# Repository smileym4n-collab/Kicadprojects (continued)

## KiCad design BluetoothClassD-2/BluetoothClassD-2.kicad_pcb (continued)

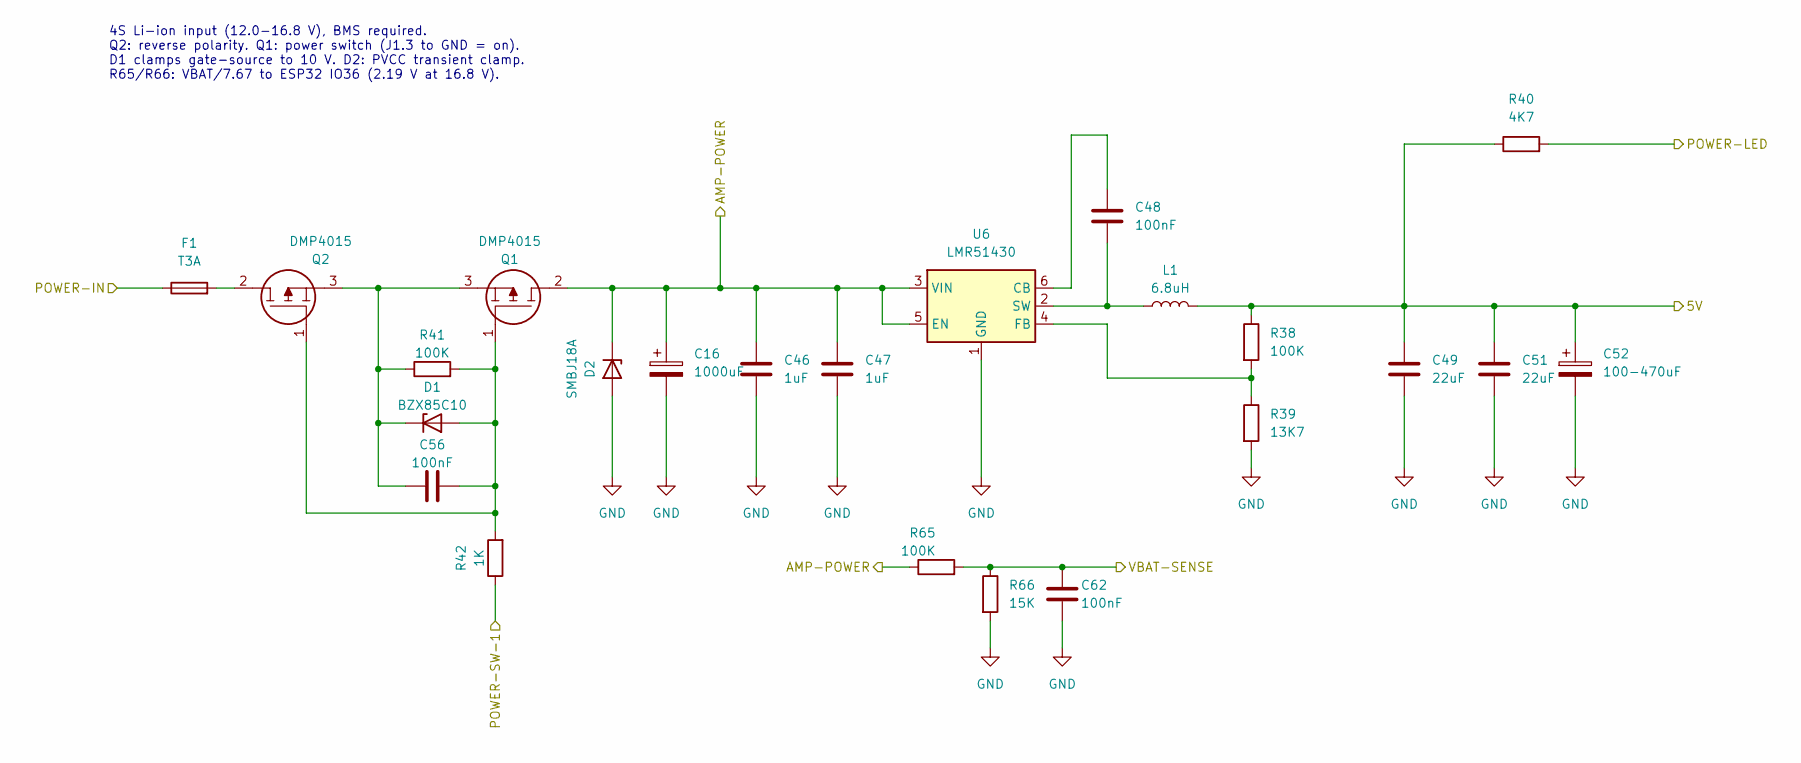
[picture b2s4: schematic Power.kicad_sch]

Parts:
C16: 1000uF; CP_Radial_D13.0mm_P5.00mm
C46, C47: 1uF; C_1206_3216Metric_Pad1.33x1.80mm_HandSolder
C48: 100nF; C_1206_3216Metric_Pad1.33x1.80mm_HandSolder
C49, C51: 22uF; C_1206_3216Metric_Pad1.33x1.80mm_HandSolder
C52: 100-470uF; CP_Radial_D8.0mm_P3.50mm
C56, C62: 100nF; C_0603_1608Metric_Pad1.08x0.95mm_HandSolder
D1: BZX85C10; D_DO-41_SOD81_P10.16mm_Horizontal; Manufacturer_Part_Number BZX85C10
D2: SMBJ18A; D_SMB; Manufacturer_Part_Number SMBJ18A
F1: T3A; Fuse_1206_3216Metric_Pad1.42x1.75mm_HandSolder
L1: 6.8uH; SRP6030WA-6R8M
Q1, Q2: DMP4015; DMP4015SK313; Manufacturer_Part_Number DMP4015SK3-13
R38, R41: 100K; R_0805_2012Metric_Pad1.20x1.40mm_HandSolder
R39: 13K7; R_0805_2012Metric_Pad1.20x1.40mm_HandSolder
R40: 4K7; R_0805_2012Metric_Pad1.20x1.40mm_HandSolder
R42: 1K; R_0805_2012Metric_Pad1.20x1.40mm_HandSolder
R65: 100K; R_0805_2012Metric_Pad1.20x1.40mm_HandSolder; Manufacturer_Part_Number RT0805DRE07100KL
R66: 15K; R_0805_2012Metric_Pad1.20x1.40mm_HandSolder; Manufacturer_Part_Number RR1220P-153-D
U6: LMR51430; SOT-23-6_Handsoldering

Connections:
/Amp/PVCC: C16.1, C46.1, C47.1, D2.1 (K), Q1.2, R65.1, U6.3 (VIN), U6.5 (EN); also elsewhere on the board
/DAC/5V: C49.1, C51.1, C52.1, L1.2, R38.1, R40.1; also elsewhere on the board
/ESP32/VBAT-SENSE: C62.1, R65.2, R66.1; also elsewhere on the board
/POWER-IN: F1.1; also elsewhere on the board
/POWER-LED: R40.2; also elsewhere on the board
/POWER-SW1: R42.1; also elsewhere on the board
GND: C16.2, C46.2, C47.2, C49.2, C51.2, C52.2, C62.2, D2.2 (A), R39.2, R66.2, U6.1 (GND); also elsewhere on the board
unnamed: C56.2, D1.2 (A), Q1.1, Q2.1, R41.2, R42.2
unnamed: C56.1, D1.1 (K), Q1.3, Q2.3, R41.1
unnamed: F1.2, Q2.2
unnamed: C48.1, U6.6 (CB)
unnamed: R38.2, R39.1, U6.4 (FB)
unnamed: C48.2, L1.1, U6.2 (SW)

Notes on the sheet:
4S Li-ion input (12.0-16.8 V), BMS required. Q2: reverse polarity. Q1: power switch (J1.3 to GND = on). D1 clamps gate-source to 10 V. D2: PVCC transient clamp. R65/R66: VBAT/7.67 to ESP32 IO36 (2.19 V at 16.8 V).

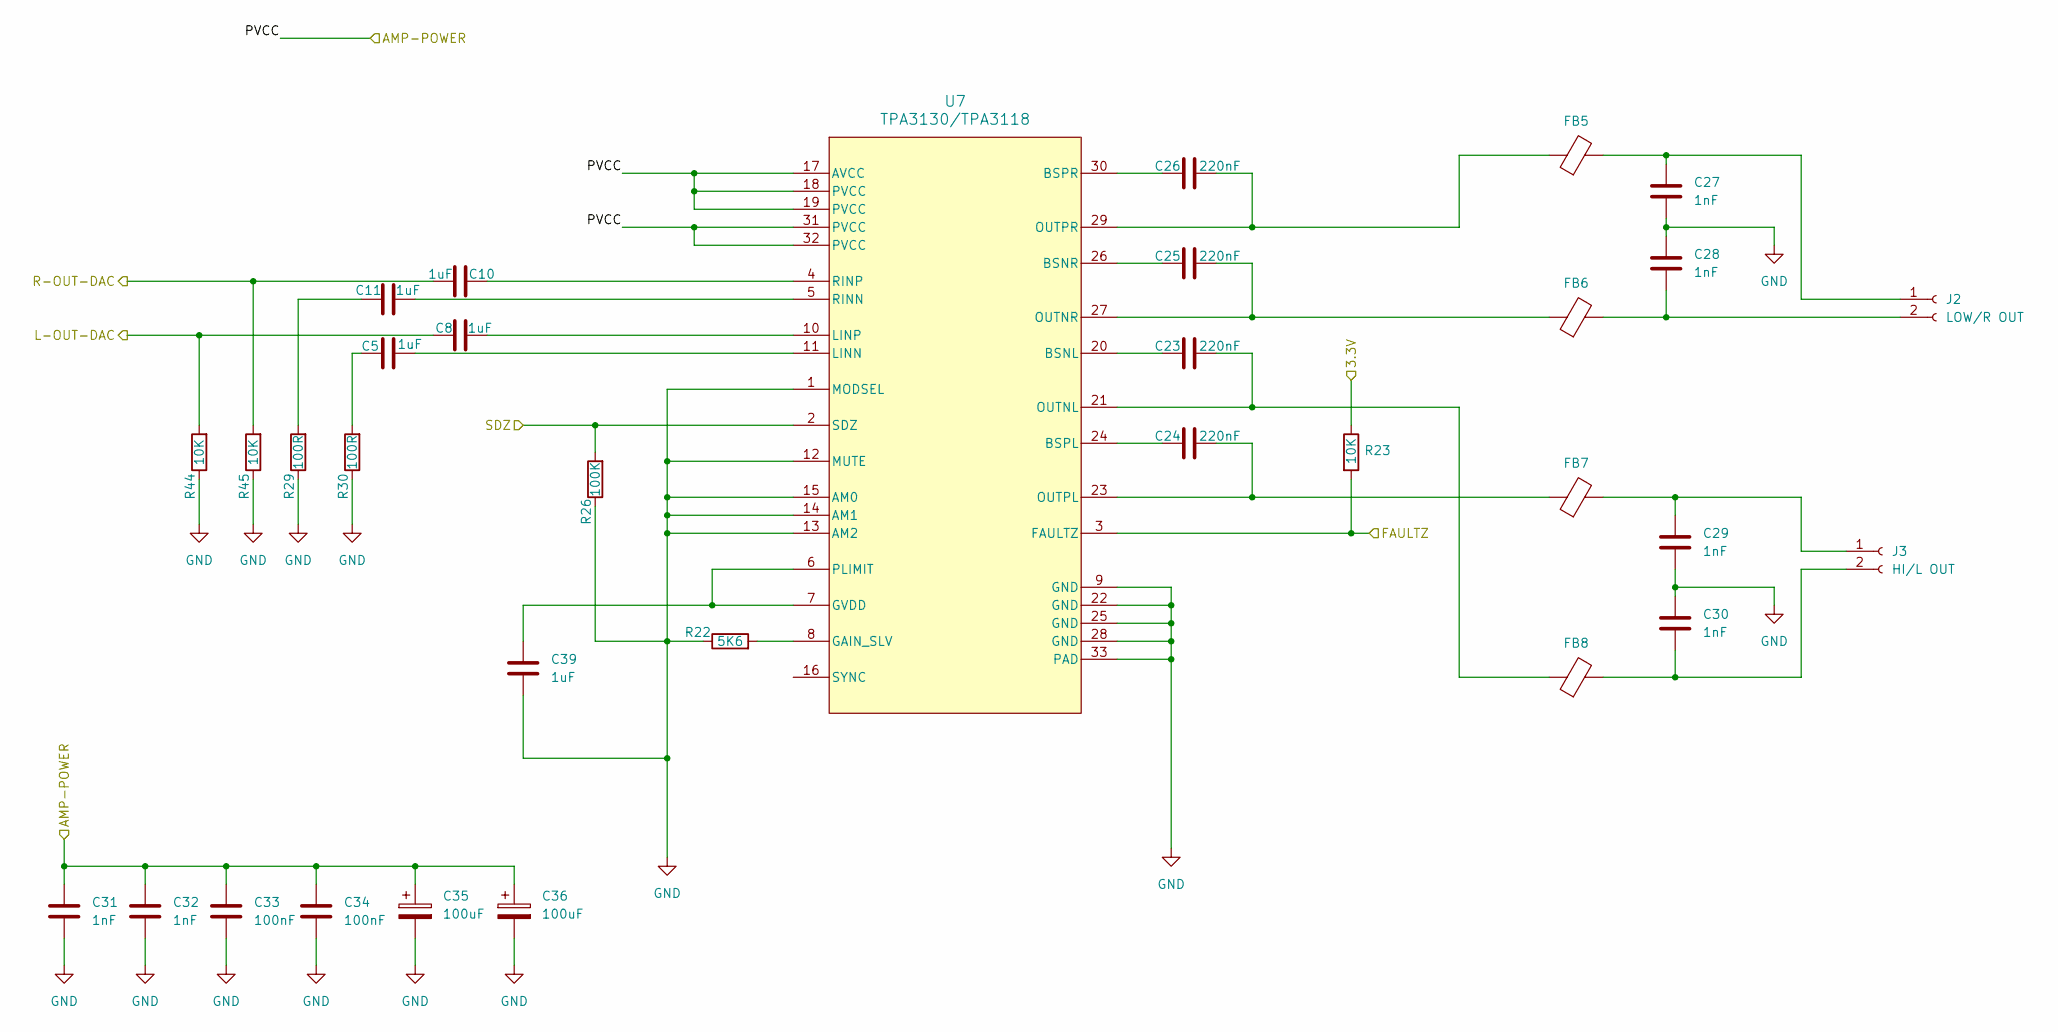
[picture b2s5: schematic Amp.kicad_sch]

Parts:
C5, C8, C10, C11: 1uF; C_Rect_L7.2mm_W5.5mm_P5.00mm_FKS2_FKP2_MKS2_MKP2
C23, C24, C25, C26: 220nF; C_0805_2012Metric_Pad1.18x1.45mm_HandSolder
C27, C28, C29, C30: 1nF; C_0805_2012Metric_Pad1.18x1.45mm_HandSolder
C31, C32: 1nF; C_0603_1608Metric_Pad1.08x0.95mm_HandSolder
C33, C34: 100nF; C_0603_1608Metric_Pad1.08x0.95mm_HandSolder
C35, C36: 100uF; CP_Radial_D8.0mm_P3.50mm
C39: 1uF; C_0805_2012Metric_Pad1.18x1.45mm_HandSolder
FB5, FB6, FB7, FB8: 74279226101; L_1812_4532Metric_Pad1.30x3.40mm_HandSolder; Manufacturer_Part_Number 74279226101
J2: LOW/R OUT; JST_XH_B2B-XH-A_1x02_P2.50mm_Vertical
J3: HI/L OUT; JST_XH_B2B-XH-A_1x02_P2.50mm_Vertical
R22: 5K6; R_0805_2012Metric_Pad1.20x1.40mm_HandSolder
R23: 10K; R_0805_2012Metric_Pad1.20x1.40mm_HandSolder
R26: 100K; R_0805_2012Metric_Pad1.20x1.40mm_HandSolder
R29, R30: 100R; R_0805_2012Metric_Pad1.20x1.40mm_HandSolder
R44, R45: 10K; R_0805_2012Metric_Pad1.20x1.40mm_HandSolder; Manufacturer_Part_Number RR1220P-103-D
U7: TPA3130/TPA3118; TPA3130D2DAPR

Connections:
/Amp/FAULTZ: R23.2, U7.3 (FAULTZ); also elsewhere on the board
/Amp/L-OUT-DAC: C8.1, R44.2; also elsewhere on the board
/Amp/PVCC: C31.1, C32.1, C33.1, C34.1, C35.1, C36.1, U7.17 (AVCC), U7.18 (PVCC), U7.19 (PVCC), U7.31 (PVCC), U7.32 (PVCC); also elsewhere on the board
/Amp/R-OUT-DAC: C10.1, R45.2; also elsewhere on the board
/Amp/SDZ: R26.2, U7.2 (SDZ); also elsewhere on the board
/ESP-3V3: R23.1; also elsewhere on the board
GND: C27.2, C28.1, C29.2, C30.1, C31.2, C32.2, C33.2, C34.2, C35.2, C36.2, C39.2, R22.1, R26.1, R29.1, R30.1, R44.1, R45.1, U7.1 (MODSEL), U7.9 (GND), U7.12 (MUTE), U7.13 (AM2), U7.14 (AM1), U7.15 (AM0), U7.22 (GND), U7.25 (GND), U7.28 (GND), U7.33 (PAD); also elsewhere on the board
unnamed: C5.1, R30.2
unnamed: C11.1, R29.2
unnamed: C27.1, FB5.2, J2.1
unnamed: C28.2, FB6.2, J2.2
unnamed: C29.1, FB7.2, J3.1
unnamed: C30.2, FB8.2, J3.2
unnamed: C23.1, U7.20 (BSNL)
unnamed: C25.1, U7.26 (BSNR)
unnamed: C24.1, U7.24 (BSPL)
unnamed: C26.1, U7.30 (BSPR)
unnamed: R22.2, U7.8 (GAIN_SLV)
unnamed: C39.1, U7.6 (PLIMIT), U7.7 (GVDD)
unnamed: C5.2, U7.11 (LINN)
unnamed: C8.2, U7.10 (LINP)
unnamed: C23.2, FB8.1, U7.21 (OUTNL)
unnamed: C25.2, FB6.1, U7.27 (OUTNR)
unnamed: C24.2, FB7.1, U7.23 (OUTPL)
unnamed: C26.2, FB5.1, U7.29 (OUTPR)
unnamed: C11.2, U7.5 (RINN)
unnamed: C10.2, U7.4 (RINP)

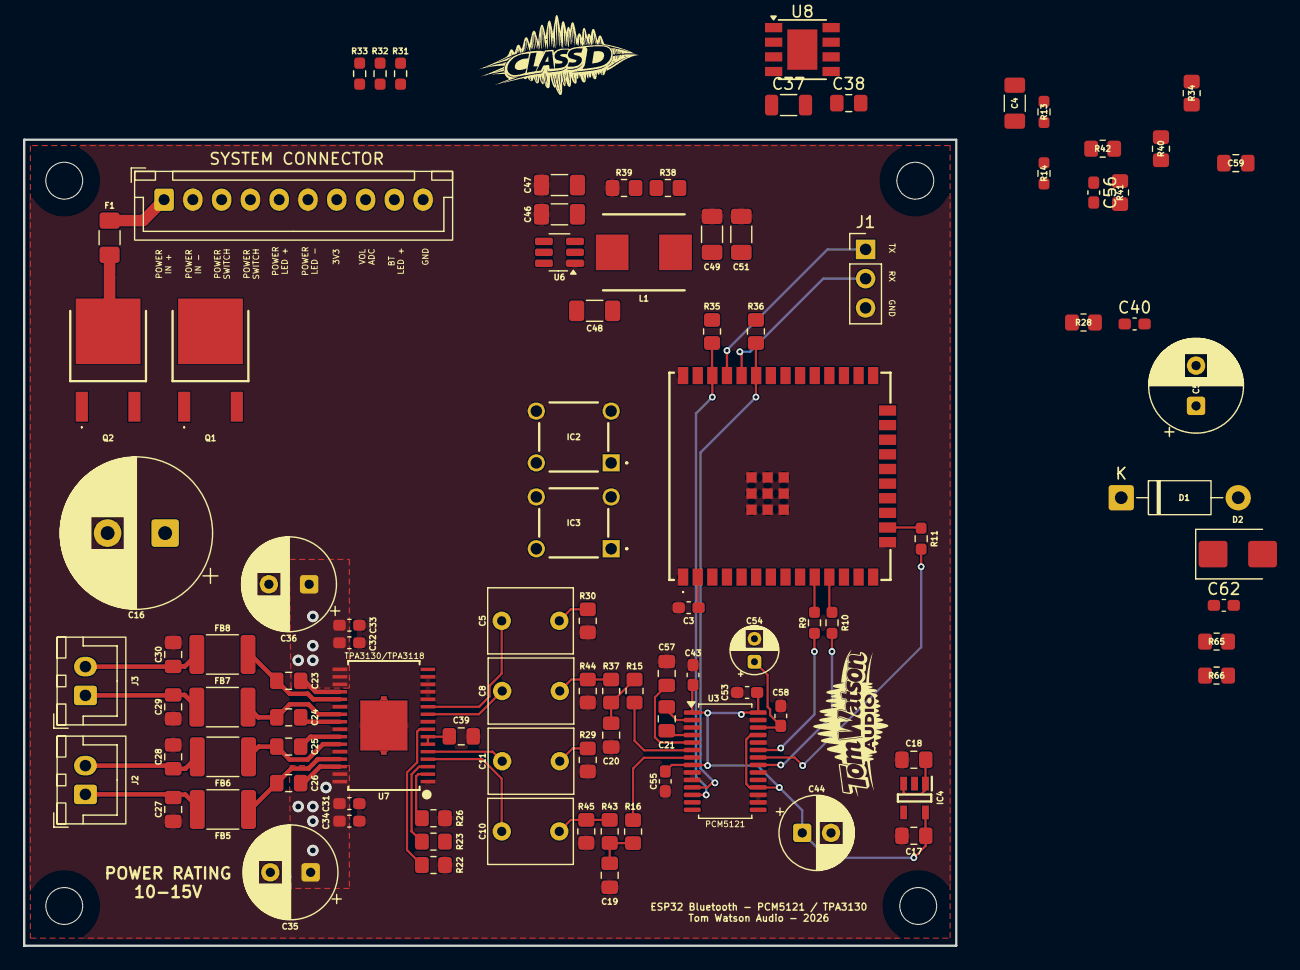
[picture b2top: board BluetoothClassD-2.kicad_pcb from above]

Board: 2 copper layers, 81.0 x 70.0 mm, 102 parts (0 on the bottom side), 64 nets.

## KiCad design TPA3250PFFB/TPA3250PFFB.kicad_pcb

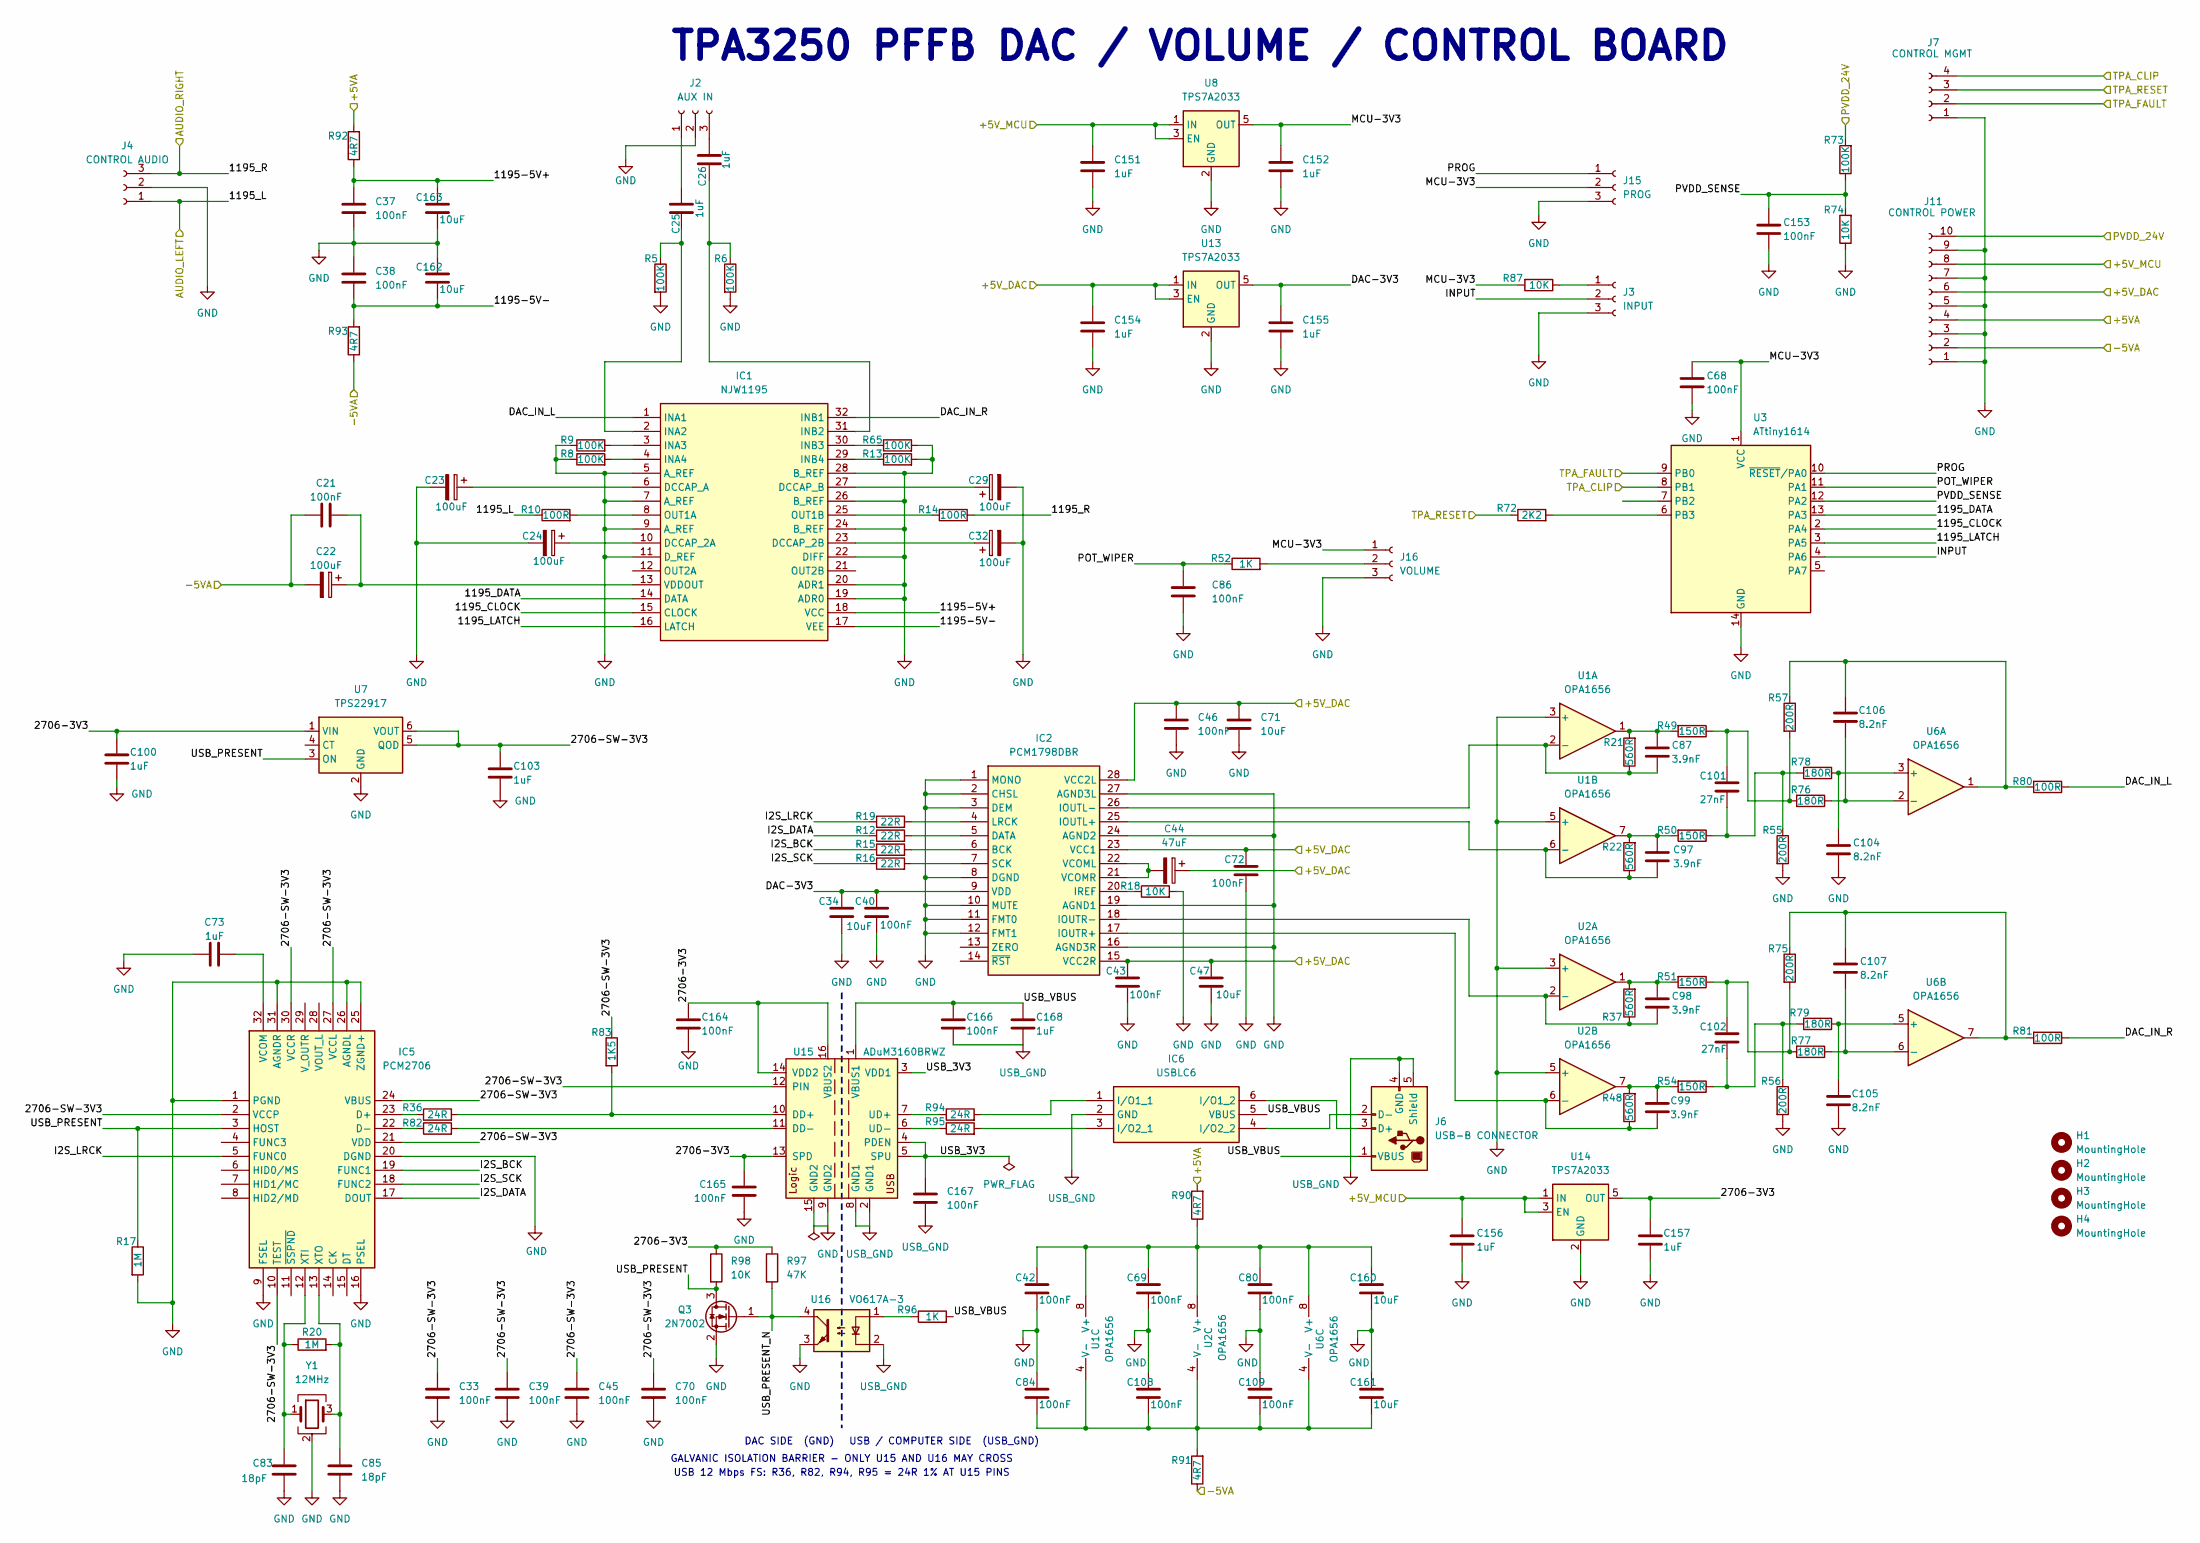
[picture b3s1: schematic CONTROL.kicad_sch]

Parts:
C21, C33, C37, C38, C39, C40, C42, C43, C45, C46, C68, C69, C70, C72, C80, C84, C86, C108, C109, C153, C164, C165, C166, C167: 100nF; C_0603_1608Metric_Pad1.08x0.95mm_HandSolder
C22, C23, C24, C29, C32: 100uF; CP_Radial_D6.3mm_P2.50mm
C25, C26: 1uF; C_Rect_L7.2mm_W5.5mm_P5.00mm_FKS2_FKP2_MKS2_MKP2
C34, C47, C71, C160, C161, C162, C163: 10uF; C_0805_2012Metric_Pad1.18x1.45mm_HandSolder
C44: 47uF; CP_Radial_D6.3mm_P2.50mm
C73, C100, C103, C151, C152, C154, C155, C156, C157, C168: 1uF; C_0805_2012Metric_Pad1.18x1.45mm_HandSolder
C83, C85: 18pF; C_0603_1608Metric_Pad1.08x0.95mm_HandSolder
C87, C97, C98, C99: 3.9nF; C_0805_2012Metric_Pad1.18x1.45mm_HandSolder
C101, C102: 27nF; C_1206_3216Metric_Pad1.33x1.80mm_HandSolder
C104, C105, C106, C107: 8.2nF; C_0805_2012Metric_Pad1.18x1.45mm_HandSolder
H1, H2, H3, H4: MountingHole; MountingHole_3.2mm_M3
IC1: NJW1195; SOP65P760X145-32N; Manufacturer_Part_Number NJW1194V-TE1; Mouser Part Number 513-NJW1194V-TE1
IC2: PCM1798DBR; SOP65P780X200-28N; Mouser Part Number 595-PCM1798DBR
IC5: PCM2706; PCM2706C; Mouser Part Number 595-PCM2706CPJTR
IC6: USBLC6; SOT-23-6_Handsoldering; Mouser Part Number 511-USBLC6-2SC6
J2: AUX IN; JST_XH_B3B-XH-A_1x03_P2.50mm_Vertical
J3: INPUT; JST_XH_B3B-XH-A_1x03_P2.50mm_Vertical
J4: CONTROL AUDIO; JST_XH_B3B-XH-A_1x03_P2.50mm_Vertical
J6: USB-B CONNECTOR; USBC
J7: CONTROL MGMT; JST_XH_B4B-XH-A_1x04_P2.50mm_Vertical
J11: CONTROL POWER; JST_XH_B10B-XH-A_1x10_P2.50mm_Vertical
J15: PROG; PinHeader_1x03_P2.54mm_Vertical
J16: VOLUME; JST_XH_B3B-XH-A_1x03_P2.50mm_Vertical
Q3: 2N7002; SOT-23
R5, R6, R8, R9, R13, R65, R73: 100K; R_0805_2012Metric_Pad1.20x1.40mm_HandSolder
R10, R14, R80, R81: 100R; R_0805_2012Metric_Pad1.20x1.40mm_HandSolder
R12, R15, R16, R19: 22R; R_0603_1608Metric_Pad0.98x0.95mm_HandSolder
R17, R20: 1M; R_0603_1608Metric_Pad0.98x0.95mm_HandSolder
R18: 10K; R_0603_1608Metric_Pad0.98x0.95mm_HandSolder
R21, R22, R37, R48: 560R; R_0805_2012Metric_Pad1.20x1.40mm_HandSolder
R36, R82, R94, R95: 24R; R_0603_1608Metric_Pad0.98x0.95mm_HandSolder; Tolerance 1%
R49, R50, R51, R54: 150R; R_0805_2012Metric_Pad1.20x1.40mm_HandSolder
R52, R96: 1K; R_0805_2012Metric_Pad1.20x1.40mm_HandSolder
R55, R56, R57, R75: 200R; R_0805_2012Metric_Pad1.20x1.40mm_HandSolder
R72: 2K2; R_0805_2012Metric_Pad1.20x1.40mm_HandSolder
R74, R87, R98: 10K; R_0805_2012Metric_Pad1.20x1.40mm_HandSolder
R76, R77, R78, R79: 180R; R_0805_2012Metric_Pad1.20x1.40mm_HandSolder
R83: 1K5; R_0603_1608Metric_Pad0.98x0.95mm_HandSolder
R90, R91, R92, R93: 4R7; R_0805_2012Metric_Pad1.20x1.40mm_HandSolder
R97: 47K; R_0805_2012Metric_Pad1.20x1.40mm_HandSolder
U1, U2, U6: OPA1656; SOIC-8_3.9x4.9mm_P1.27mm
U3: ATtiny1614; SOIC-14_3.9x8.7mm_P1.27mm
U7: TPS22917; SOT-23-6
U8, U13, U14: TPS7A2033; SOT-23-5
U15: ADuM3160BRWZ; SOIC-16W_7.5x10.3mm_P1.27mm
U16: VO617A-3; DIP-4_W7.62mm
Y1: 12MHz; Crystal_SMD_3225-4Pin_3.2x2.5mm

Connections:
/AMP/IN_L: J4.1, R10.1; also elsewhere on the board
/AMP/IN_R: J4.3, R14.2; also elsewhere on the board
/AMP/PVDD_24V: J11.10, R73.2; also elsewhere on the board
/AMP/TPA_CLIP: J7.4, U3.8 (PB1); also elsewhere on the board
/AMP/TPA_FAULT: J7.2, U3.9 (PB0); also elsewhere on the board
/AMP/TPA_RESET: J7.3, R72.1; also elsewhere on the board
/CONTROL/1195-5V+: C37.1, C163.1, IC1.18 (VCC), R92.1
/CONTROL/1195-5V-: C38.2, C162.2, IC1.17 (VEE), R93.2
/CONTROL/1195_CLOCK: IC1.15 (CLOCK), U3.2 (PA4)
/CONTROL/1195_DATA: IC1.14 (DATA), U3.13 (PA3)
/CONTROL/1195_LATCH: IC1.16 (LATCH), U3.3 (PA5)
/CONTROL/2706-3V3: C100.1, C157.1, C164.1, C165.1, R97.1, R98.1, U7.1 (VIN), U14.5 (OUT), U15.13 (SPD), U15.14 (VDD2), U15.16 (VBUS2)
/CONTROL/2706-SW-3V3: C33.1, C39.1, C45.1, C70.1, C103.1, IC5.2 (VCCP), IC5.10 (TEST), IC5.21 (VDD), IC5.24 (VBUS), IC5.27 (VCCL), IC5.30 (VCCR), R83.1, U7.5 (QOD), U7.6 (VOUT), U15.12 (PIN)
/CONTROL/+5VA: J11.4, R90.2, R92.2; also elsewhere on the board
/CONTROL/+5V_DAC: C43.1, C44.1, C46.1, C47.1, C71.1, C72.1, C154.1, IC2.15 (VCC2R), IC2.23 (VCC1), IC2.28 (VCC2L), J11.6, U13.1 (IN), U13.3 (EN); also elsewhere on the board
/CONTROL/+5V_MCU: C151.1, C156.1, J11.8, U8.1 (IN), U8.3 (EN), U14.1 (IN), U14.3 (EN); also elsewhere on the board
/CONTROL/-5VA: C21.1, C22.2, J11.2, R91.1, R93.1; also elsewhere on the board
/CONTROL/DAC-3V3: C34.1, C40.1, C155.1, IC2.9 (VDD), U13.5 (OUT)
/CONTROL/DAC_IN_L: IC1.1 (INA1), R80.1
/CONTROL/DAC_IN_R: IC1.32 (INB1), R81.1
/CONTROL/I2S_BCK: IC5.19 (FUNC1), R15.1
/CONTROL/I2S_DATA: IC5.17 (DOUT), R12.1
/CONTROL/I2S_LRCK: IC5.5 (FUNC0), R19.1
/CONTROL/I2S_SCK: IC5.18 (FUNC2), R16.1
/CONTROL/INPUT: J3.2, U3.4 (PA6)
/CONTROL/MCU-3V3: C68.1, C152.1, J15.2, J16.1, R87.2, U3.1 (VCC), U8.5 (OUT)
/CONTROL/POT_WIPER: C86.1, R52.1, U3.11 (PA1)
/CONTROL/PROG: J15.1, U3.10 (~RESET/PA0)
/CONTROL/PVDD_SENSE: C153.1, R73.1, R74.2, U3.12 (PA2)
/CONTROL/USB_3V3: C167.1, U15.3 (VDD1), U15.4 (PDEN), U15.5 (SPU)
/CONTROL/USB_PRESENT: IC5.3 (HOST), Q3.3 (D), R17.1, R98.2, U7.3 (ON)
/CONTROL/USB_PRESENT_N: Q3.1 (G), R97.2, U16.4
/CONTROL/USB_VBUS: C166.1, C168.1, IC6.5 (VBUS), J6.1 (VBUS), R96.2, U15.1 (VBUS1)
GND: C23.2, C24.2, C29.2, C32.2, C33.2, C34.2, C37.2, C38.1, C39.2, C40.2, C42.2, C43.2, C45.2, C46.2, C47.2, C68.2, C69.2, C70.2, C71.2, C72.2, C73.1, C80.2, C83.2, C84.1, C85.2, C86.2, C100.2, C103.2, C104.2, C105.2, C108.1, C109.1, C151.2, C152.2, C153.2, C154.2, C155.2, C156.2, C157.2, C160.2, C161.1, C162.1, C163.2, C164.2, C165.2, IC1.5 (A_REF), IC1.7 (A_REF), IC1.9 (A_REF), IC1.11 (D_REF), IC1.19 (ADR0), IC1.20 (ADR1), IC1.22 (DIFF), IC1.24 (B_REF), IC1.26 (B_REF), IC1.28 (B_REF), IC2.1 (MONO), IC2.2 (CHSL), IC2.3 (DEM), IC2.8 (DGND), IC2.10 (MUTE), IC2.11 (FMT0), IC2.12 (FMT1), IC2.16 (AGND3R), IC2.19 (AGND1), IC2.24 (AGND2), IC2.27 (AGND3L), IC5.1 (PGND), IC5.9 (FSEL), IC5.16 (PSEL), IC5.20 (DGND), IC5.25 (ZGND+), IC5.26 (AGNDL), IC5.31 (AGNDR), J2.2, J3.3, J4.2, J7.1, J11.1, J11.3, J11.5, J11.7, J11.9, J15.3, J16.3, Q3.2 (S), R5.2, R6.2, R8.1, R9.1, R13.2, R17.2, R18.2, R55.2, R56.2, R65.2, R74.1, U1.3 (+), U1.5 (+), U2.3 (+), U2.5 (+), U3.14 (GND), U7.2 (GND), U8.2 (GND), U13.2 (GND), U14.2 (GND), U15.9 (GND2), U15.15 (GND2), U16.3, Y1.2 (G), Y1.4 (G); also elsewhere on the board
unnamed: C87.2, R21.2, R49.2, U1.1
unnamed: C97.2, R22.2, R50.2, U1.7
unnamed: C98.2, R37.2, R51.2, U2.1
unnamed: C99.2, R48.2, R54.2, U2.7
unnamed: C101.1, R49.1, R57.2, R76.2
unnamed: C101.2, R50.1, R55.1, R78.2
unnamed: C102.1, R51.1, R75.2, R77.2
unnamed: C102.2, R54.1, R56.1, R79.2
unnamed: C106.1, R57.1, R80.2, U6.1
unnamed: C107.1, R75.1, R81.2, U6.7
unnamed: C24.1, IC1.10 (DCCAP_2A)
unnamed: C32.1, IC1.23 (DCCAP_2B)
unnamed: C23.1, IC1.6 (DCCAP_A)
unnamed: C29.1, IC1.27 (DCCAP_B)
unnamed: C25.2, IC1.2 (INA2), R5.1
unnamed: IC1.3 (INA3), R9.2
unnamed: IC1.4 (INA4), R8.2
unnamed: C26.2, IC1.31 (INB2), R6.1
unnamed: IC1.30 (INB3), R65.1
unnamed: IC1.29 (INB4), R13.1
unnamed: IC1.8 (OUT1A), R10.2
unnamed: IC1.25 (OUT1B), R14.1
unnamed: C21.2, C22.1, IC1.13 (VDDOUT)
unnamed: IC2.6 (BCK), R15.2
unnamed: IC2.5 (DATA), R12.2
unnamed: C97.1, IC2.25 (IOUTL+), R22.1, U1.6 (-)
unnamed: C87.1, IC2.26 (IOUTL-), R21.1, U1.2 (-)
unnamed: C99.1, IC2.17 (IOUTR+), R48.1, U2.6 (-)
unnamed: C98.1, IC2.18 (IOUTR-), R37.1, U2.2 (-)
unnamed: IC2.20 (IREF), R18.1
unnamed: IC2.4 (LRCK), R19.2
unnamed: IC2.7 (SCK), R16.2
unnamed: C44.2, IC2.21 (VCOMR), IC2.22 (VCOML)
unnamed: IC5.23 (D+), R36.1
unnamed: IC5.22 (D-), R82.1
unnamed: C73.2, IC5.32 (VCOM)
unnamed: C83.1, IC5.12 (XTI), R20.1, Y1.1
unnamed: C85.1, IC5.13 (XTO), R20.2, Y1.3
unnamed: IC6.1 (I/O1_1), R94.2
unnamed: IC6.6 (I/O1_2), J6.3 (D+)
unnamed: IC6.3 (I/O2_1), R95.2
unnamed: IC6.4 (I/O2_2), J6.2 (D-)
unnamed: C25.1, J2.1
unnamed: C26.1, J2.3
unnamed: J3.1, R87.1
unnamed: J16.2, R52.2
unnamed: R96.1, U16.1
unnamed: C42.1, C69.1, C80.1, C160.1, R90.1, U1.8 (V+), U2.8 (V+), U6.8 (V+)
unnamed: C84.2, C108.2, C109.2, C161.2, R91.2, U1.4 (V-), U2.4 (V-), U6.4 (V-)
unnamed: R72.2, U3.6 (PB3)
unnamed: C104.1, R78.1, U6.3 (+)
unnamed: C106.2, R76.1, U6.2 (-)
unnamed: C105.1, R79.1, U6.5 (+)
unnamed: C107.2, R77.1, U6.6 (-)
unnamed: R36.2, R83.2, U15.10 (DD+)
unnamed: R82.2, U15.11 (DD-)
unnamed: R94.1, U15.7 (UD+)
unnamed: R95.1, U15.6 (UD-)
USB_GND: C166.2, C167.2, C168.2, IC6.2 (GND), J6.4 (GND), J6.5 (Shield), U15.2 (GND1), U15.8 (GND1), U16.2

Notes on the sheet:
GALVANIC ISOLATION BARRIER - ONLY U15 AND U16 MAY CROSS
TPA3250 PFFB DAC / VOLUME / CONTROL BOARD
USB / COMPUTER SIDE (USB_GND)
USB 12 Mbps FS: R36, R82, R94, R95 = 24R 1% AT U15 PINS
DAC SIDE (GND)

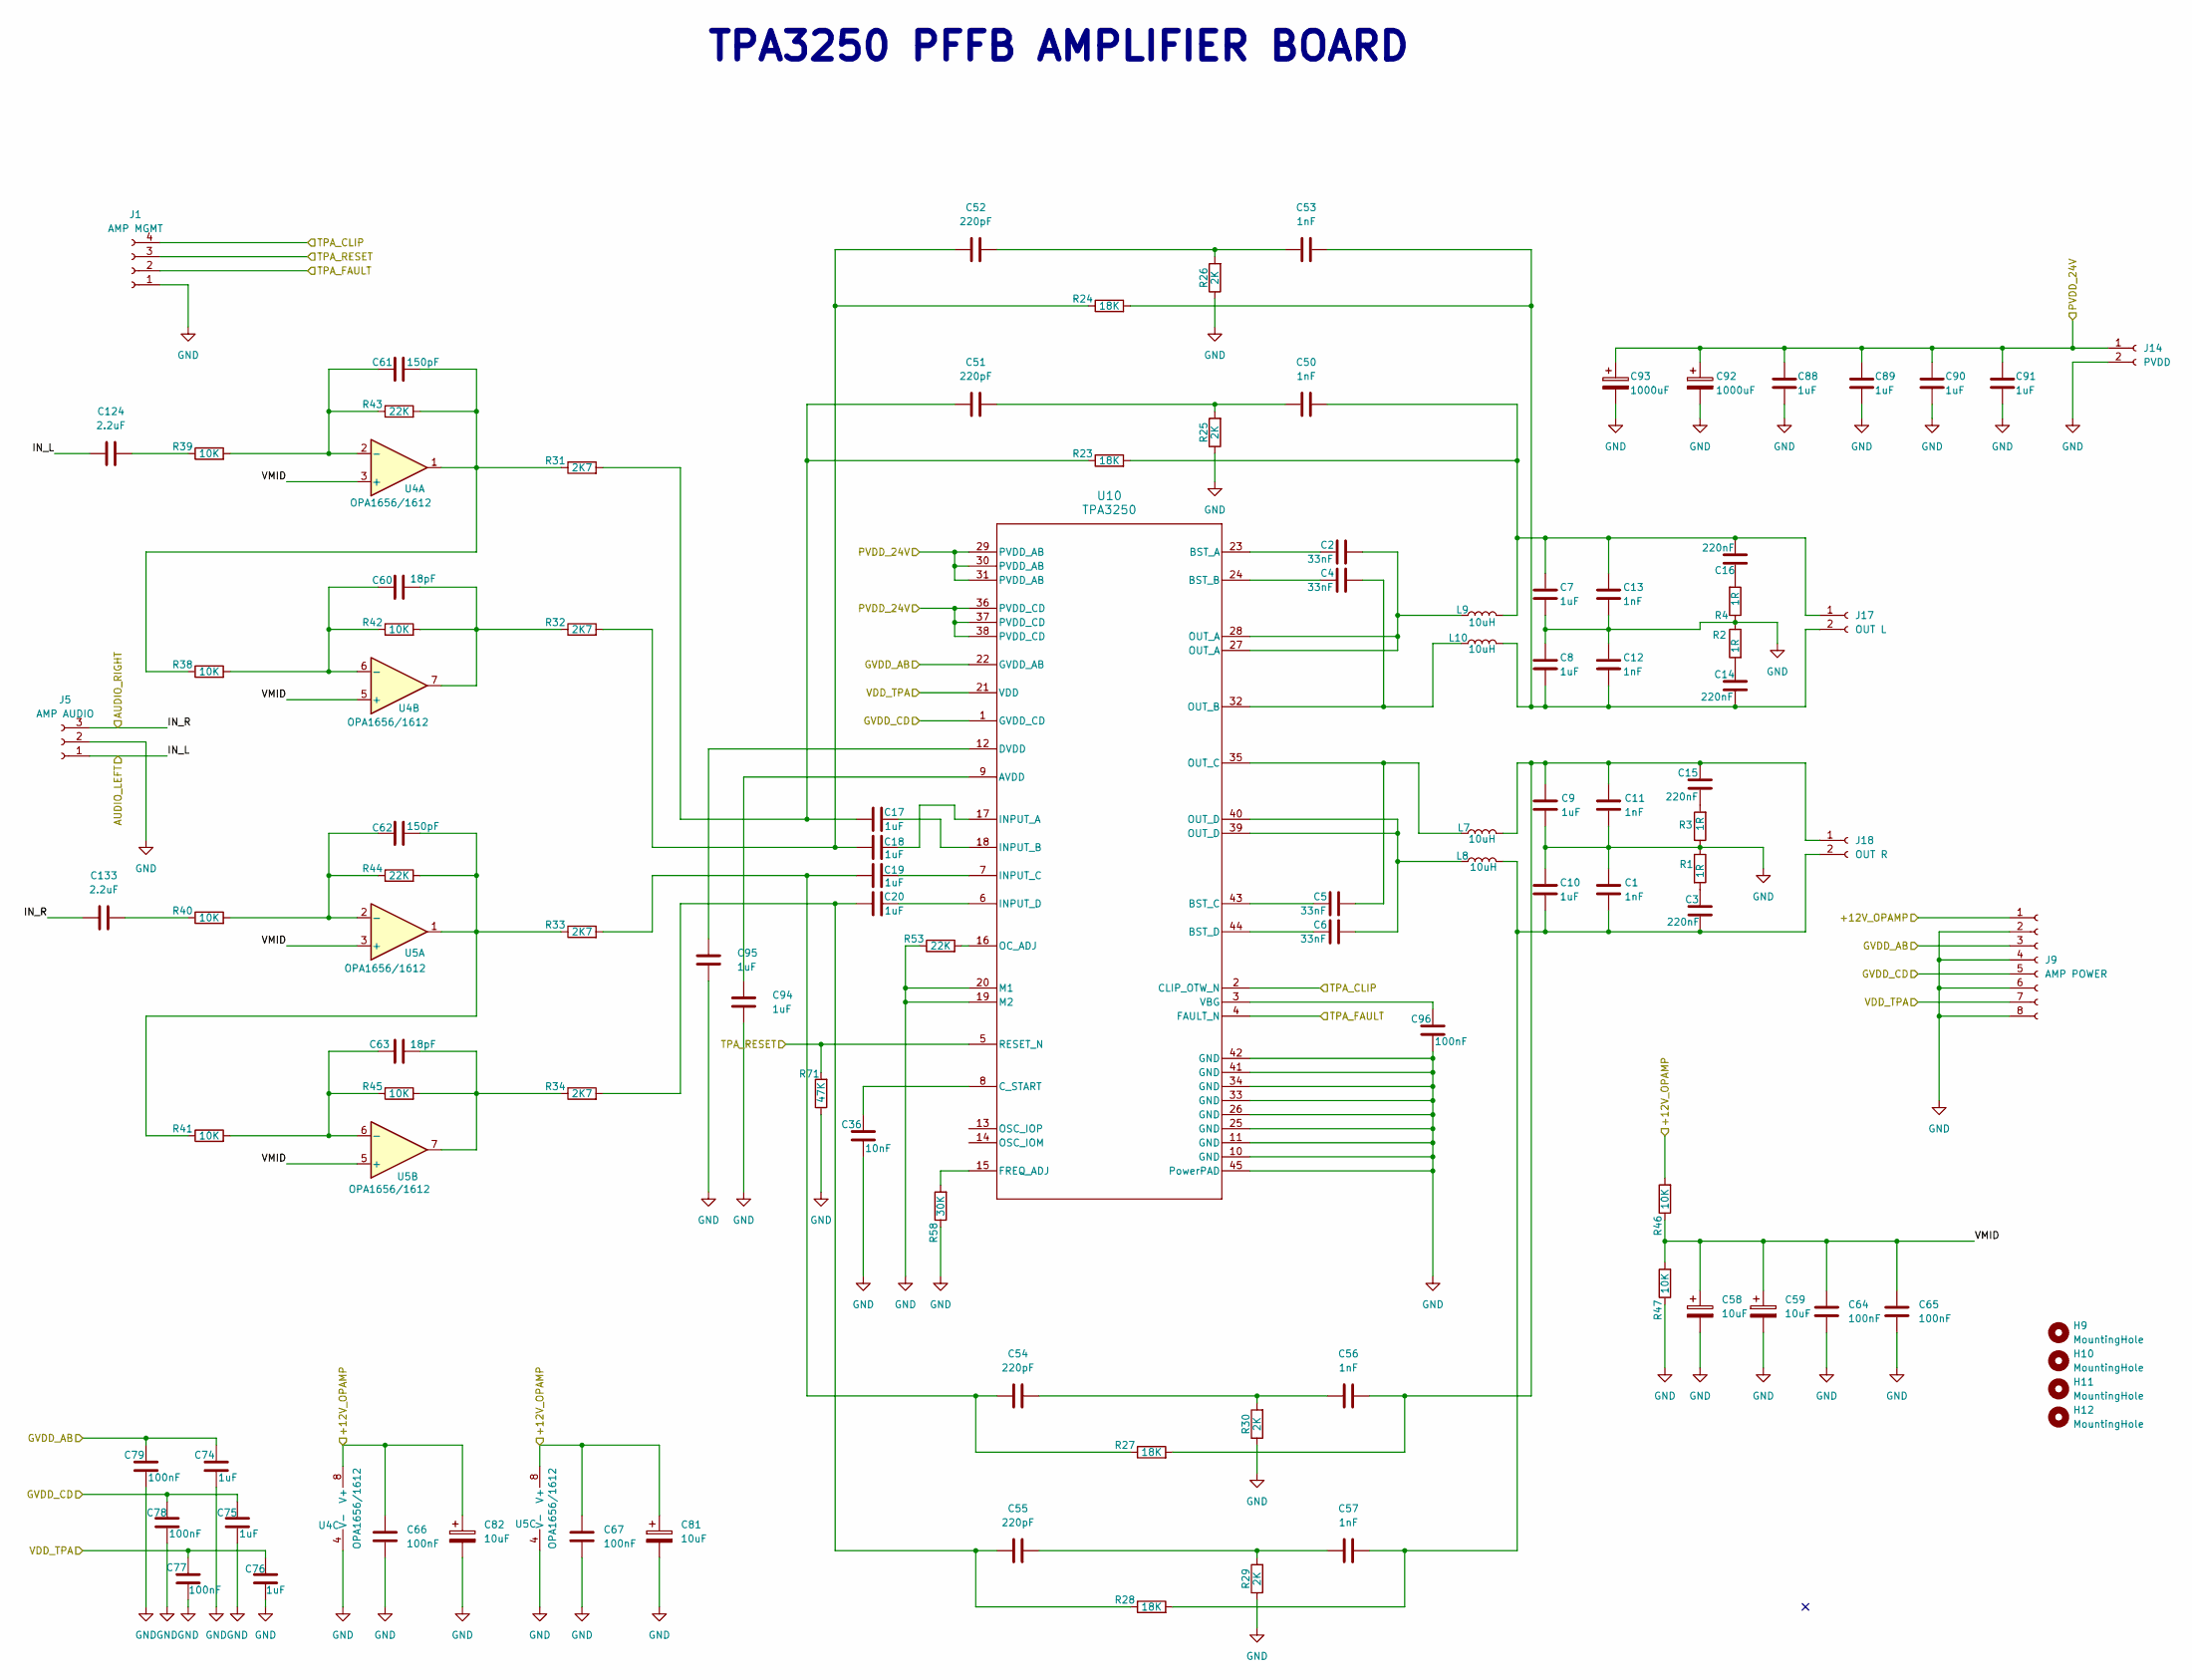
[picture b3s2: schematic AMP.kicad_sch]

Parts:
C1, C11, C12, C13, C50, C53, C56, C57: 1nF; C_0805_2012Metric_Pad1.18x1.45mm_HandSolder
C2, C4, C5, C6: 33nF; C_0805_2012Metric_Pad1.18x1.45mm_HandSolder
C3, C14, C15, C16: 220nF; C_1206_3216Metric_Pad1.33x1.80mm_HandSolder
C7, C8, C9, C10: 1uF; C_Rect_L18.0mm_W8.0mm_P15.00mm_FKS3_FKP3
C17, C18, C19, C20: 1uF; C_Rect_L7.2mm_W5.5mm_P5.00mm_FKS2_FKP2_MKS2_MKP2
C36: 10nF; C_0805_2012Metric_Pad1.18x1.45mm_HandSolder
C51, C52, C54, C55: 220pF; C_0805_2012Metric_Pad1.18x1.45mm_HandSolder
C58, C59, C81, C82: 10uF; CP_Radial_D4.0mm_P2.00mm
C60, C63: 18pF; C_0603_1608Metric_Pad1.08x0.95mm_HandSolder
C61, C62: 150pF; C_0805_2012Metric_Pad1.18x1.45mm_HandSolder
C64, C65, C66, C67, C77, C78, C79, C96: 100nF; C_0603_1608Metric_Pad1.08x0.95mm_HandSolder
C74, C75, C76, C94, C95: 1uF; C_0805_2012Metric_Pad1.18x1.45mm_HandSolder
C88, C89, C90, C91: 1uF; C_1206_3216Metric_Pad1.33x1.80mm_HandSolder
C92, C93: 1000uF; CP_Radial_D12.5mm_P5.00mm
C124, C133: 2.2uF; C_Rect_L7.2mm_W7.2mm_P5.00mm_FKS2_FKP2_MKS2_MKP2
H9, H10, H11, H12: MountingHole; MountingHole_3.2mm_M3
J1: AMP MGMT; JST_XH_B4B-XH-A_1x04_P2.50mm_Vertical
J5: AMP AUDIO; JST_XH_B3B-XH-A_1x03_P2.50mm_Vertical
J9: AMP POWER; JST_XH_B8B-XH-A_1x08_P2.50mm_Vertical
J14: PVDD; Molex_KK-396_A-41791-0002_1x02_P3.96mm_Vertical
J17: OUT L; Molex_KK-396_A-41791-0002_1x02_P3.96mm_Vertical
J18: OUT R; Molex_KK-396_A-41791-0002_1x02_P3.96mm_Vertical
L7, L8, L9, L10: 10uH; L_Wuerth_HCI-1350
R1, R2, R3, R4: 1R; R_2512_6332Metric_Pad1.40x3.35mm_HandSolder
R23, R24, R27, R28: 18K; R_0805_2012Metric_Pad1.20x1.40mm_HandSolder
R25, R26, R29, R30: 2K; R_0805_2012Metric_Pad1.20x1.40mm_HandSolder
R31, R32, R33, R34: 2K7; R_0805_2012Metric_Pad1.20x1.40mm_HandSolder
R38, R39, R40, R41, R42, R45, R46, R47: 10K; R_0805_2012Metric_Pad1.20x1.40mm_HandSolder
R43, R44, R53: 22K; R_0805_2012Metric_Pad1.20x1.40mm_HandSolder
R58: 30K; R_0805_2012Metric_Pad1.20x1.40mm_HandSolder
R71: 47K; R_0805_2012Metric_Pad1.20x1.40mm_HandSolder
U4, U5: OPA1656/1612; SOIC-8_3.9x4.9mm_P1.27mm
U10: TPA3250

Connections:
/AMP/+12V_OPAMP: C66.1, C67.1, C81.1, C82.1, J9.1, R46.2, U4.8 (V+), U5.8 (V+); also elsewhere on the board
/AMP/GVDD_AB: C74.1, C79.1, J9.3, U10.22 (GVDD_AB); also elsewhere on the board
/AMP/GVDD_CD: C75.1, C78.1, J9.5, U10.1 (GVDD_CD); also elsewhere on the board
/AMP/IN_L: C124.1, J5.1; also elsewhere on the board
/AMP/IN_R: C133.1, J5.3; also elsewhere on the board
/AMP/PVDD_24V: C88.1, C89.1, C90.1, C91.1, C92.1, C93.1, J14.1, U10.29 (PVDD_AB), U10.30 (PVDD_AB), U10.31 (PVDD_AB), U10.36 (PVDD_CD), U10.37 (PVDD_CD), U10.38 (PVDD_CD); also elsewhere on the board
/AMP/TPA_CLIP: J1.4, U10.2 (CLIP_OTW_N); also elsewhere on the board
/AMP/TPA_FAULT: J1.2, U10.4 (FAULT_N); also elsewhere on the board
/AMP/TPA_RESET: J1.3, R71.2, U10.5 (RESET_N); also elsewhere on the board
/AMP/VDD_TPA: C76.1, C77.1, J9.7, U10.21 (VDD); also elsewhere on the board
/AMP/VMID: C58.1, C59.1, C64.1, C65.1, R46.1, R47.2, U4.3 (+), U4.5 (+), U5.3 (+), U5.5 (+)
GND: C1.1, C7.1, C8.2, C9.1, C10.2, C11.2, C12.1, C13.2, C36.2, C58.2, C59.2, C64.2, C65.2, C66.2, C67.2, C74.2, C75.2, C76.2, C77.2, C78.2, C79.2, C81.2, C82.2, C88.2, C89.2, C90.2, C91.2, C92.2, C93.2, C94.2, C95.2, C96.2, J1.1, J5.2, J9.2, J9.4, J9.6, J9.8, J14.2, R1.1, R2.1, R3.1, R4.1, R25.1, R26.1, R29.1, R30.1, R47.1, R53.1, R58.1, R71.1, U4.4 (V-), U5.4 (V-), U10.10 (GND), U10.11 (GND), U10.19 (M2), U10.20 (M1), U10.25 (GND), U10.26 (GND), U10.33 (GND), U10.34 (GND), U10.41 (GND), U10.42 (GND), U10.45 (PowerPAD); also elsewhere on the board
unnamed: C2.2, L9.1, U10.27 (OUT_A), U10.28 (OUT_A)
unnamed: C3.1, R1.2
unnamed: C6.2, L8.1, U10.39 (OUT_D), U10.40 (OUT_D)
unnamed: C14.1, R2.2
unnamed: C15.1, R3.2
unnamed: C16.1, R4.2
unnamed: C17.1, C51.1, R23.1, R31.2
unnamed: C18.1, C52.1, R24.1, R32.2
unnamed: C19.1, C54.1, R27.1, R33.2
unnamed: C20.1, C55.1, R28.1, R34.2
unnamed: C50.1, C51.2, R25.2
unnamed: C52.2, C53.1, R26.2
unnamed: C54.2, C56.1, R30.2
unnamed: C55.2, C57.1, R29.2
unnamed: C60.2, R32.1, R42.2, U4.7
unnamed: C61.2, R31.1, R38.1, R43.2, U4.1
unnamed: C62.2, R33.1, R41.1, R44.2, U5.1
unnamed: C63.2, R34.1, R45.2, U5.7
unnamed: C124.2, R39.1
unnamed: C133.2, R40.1
unnamed: C7.2, C13.1, C16.2, C50.2, J17.1, L9.2, R23.2
unnamed: C8.1, C12.2, C14.2, C53.2, J17.2, L10.2, R24.2
unnamed: C9.2, C11.1, C15.2, C56.2, J18.1, L7.2, R27.2
unnamed: C1.2, C3.2, C10.1, C57.2, J18.2, L8.2, R28.2
unnamed: C61.1, R39.2, R43.1, U4.2 (-)
unnamed: C60.1, R38.2, R42.1, U4.6 (-)
unnamed: C62.1, R40.2, R44.1, U5.2 (-)
unnamed: C63.1, R41.2, R45.1, U5.6 (-)
unnamed: C94.1, U10.9 (AVDD)
unnamed: C2.1, U10.23 (BST_A)
unnamed: C4.1, U10.24 (BST_B)
unnamed: C5.1, U10.43 (BST_C)
unnamed: C6.1, U10.44 (BST_D)
unnamed: C36.1, U10.8 (C_START)
unnamed: C95.1, U10.12 (DVDD)
unnamed: R58.2, U10.15 (FREQ_ADJ)
unnamed: C18.2, U10.17 (INPUT_A)
unnamed: C17.2, U10.18 (INPUT_B)
unnamed: C19.2, U10.7 (INPUT_C)
unnamed: C20.2, U10.6 (INPUT_D)
unnamed: R53.2, U10.16 (OC_ADJ)
unnamed: C4.2, L10.1, U10.32 (OUT_B)
unnamed: C5.2, L7.1, U10.35 (OUT_C)
unnamed: C96.1, U10.3 (VBG)

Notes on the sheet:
TPA3250 PFFB AMPLIFIER BOARD
